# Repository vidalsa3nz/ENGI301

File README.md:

# ENGI301
<ENGI301>
Repository for ENGI301 course work

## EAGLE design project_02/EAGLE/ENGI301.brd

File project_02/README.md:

# ENGI 301: Etch A Sketch

This folder has files for the electronic components of the Etch A Sketch device including .sch, .brd, .lib, and other miscellaneous files.
For this project we were given components to go into the Etch A Sketch device and were tasked with creating the above files using symbols and footprints for each component.

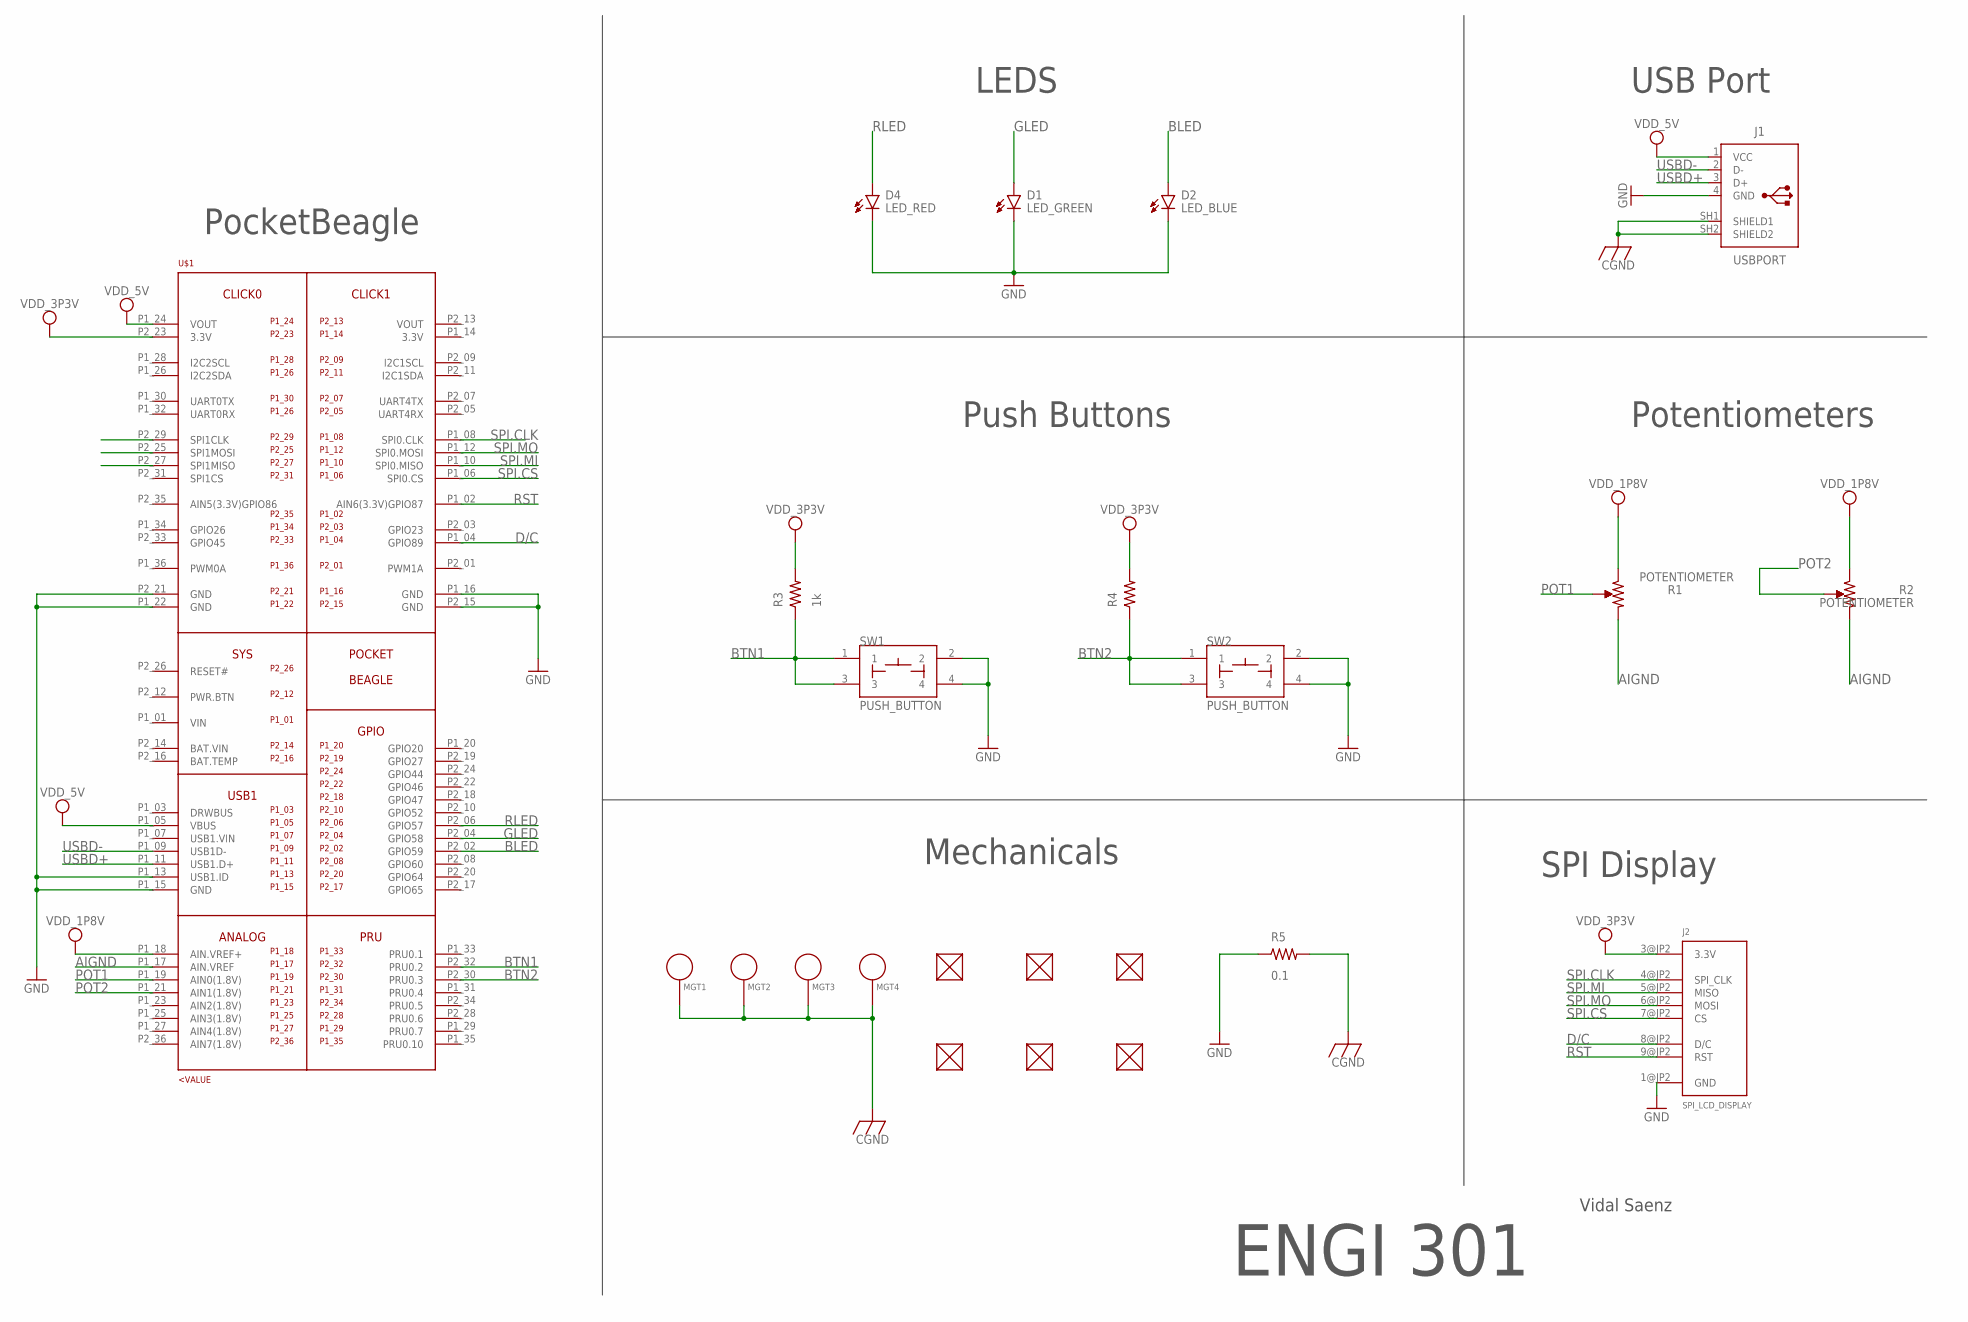
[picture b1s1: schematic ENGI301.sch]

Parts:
D1: LED_GREEN; LEDC3216X75N_FLAT-G
D2: LED_BLUE; LEDC3216X75N_FLAT-B
D4: LED_RED; LEDC3216X75N_FLAT-R
FUD1, FUD2, FUD3, FUD4, FUD5, FUD6: FIDUCIAL; FIDUCIAL_40MIL
J1: USBPORT; 1734366
J2: SPI_LCD_DISPLAY
MGT1, MGT2, MGT3, MGT4: MOUNTING_HOLE
R1, R2: POTENTIOMETER; POT-PO90S
R3: 1k; R1206
R4: R_R1206; R1206
R5: 0.1; R0603
SW1, SW2: PUSH_BUTTON; BUTTON_12.5MM
U$1: POCKETBEAGLE

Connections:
AIGND: R1.CW, R2.CW, U$1.P1_17 (AIN.VREF)
BLED: D2.A, U$1.P2_02 (GPIO59)
BTN1: R3.1, SW1.1, SW1.3, U$1.P2_32 (PRU0.2)
BTN2: R4.1, SW2.1, SW2.3, U$1.P2_30 (PRU0.3)
CGND: MGT1.P$1, MGT2.P$1, MGT3.P$1, MGT4.P$1, R5.2
D/C: J2.8@JP2 (D/C), U$1.P1_04 (GPIO89)
GLED: D1.A, U$1.P2_04 (GPIO58)
GND: J1.4 (GND), J2.1@JP2 (GND), R5.1, SW1.2, SW1.4, SW2.2, SW2.4, U$1.P1_13 (USB1.ID), U$1.P1_15 (GND), U$1.P1_16 (GND), U$1.P1_22 (GND), U$1.P2_15 (GND), U$1.P2_21 (GND)
unnamed: D1.C, D2.C, D4.C
POT1: R1.S, U$1.P1_19 (AIN0(1.8V))
POT2: R2.S, U$1.P1_21 (AIN1(1.8V))
RLED: D4.A, U$1.P2_06 (GPIO57)
RST: J2.9@JP2 (RST), U$1.P1_02 (AIN6(3.3V)GPIO87)
SHIELD2: J1.SH1 (SHIELD1), J1.SH2 (SHIELD2)
SPI.CLK: J2.4@JP2 (SPI_CLK), U$1.P1_08 (SPI0.CLK)
SPI.CS: J2.7@JP2 (CS), U$1.P1_06 (SPI0.CS)
SPI.MI: J2.5@JP2 (MISO), U$1.P1_10 (SPI0.MISO)
SPI.MO: J2.6@JP2 (MOSI), U$1.P1_12 (SPI0.MOSI)
USBD+: J1.3 (D+), U$1.P1_11 (USB1.D+)
USBD-: J1.2 (D-), U$1.P1_09 (USB1D-)
VDD_1P8V: R1.CCW, R2.CCW, U$1.P1_18 (AIN.VREF+)
VDD_3P3V: J2.3@JP2 (3.3V), R3.2, R4.2, U$1.P2_23 (3.3V)
VDD_5V: J1.1 (VCC), U$1.P1_05 (VBUS), U$1.P1_24 (VOUT)

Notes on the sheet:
PocketBeagle
SPI Display
USB Port
Push Buttons
Potentiometers
LEDS
Mechanicals
Vidal Saenz
ENGI 301

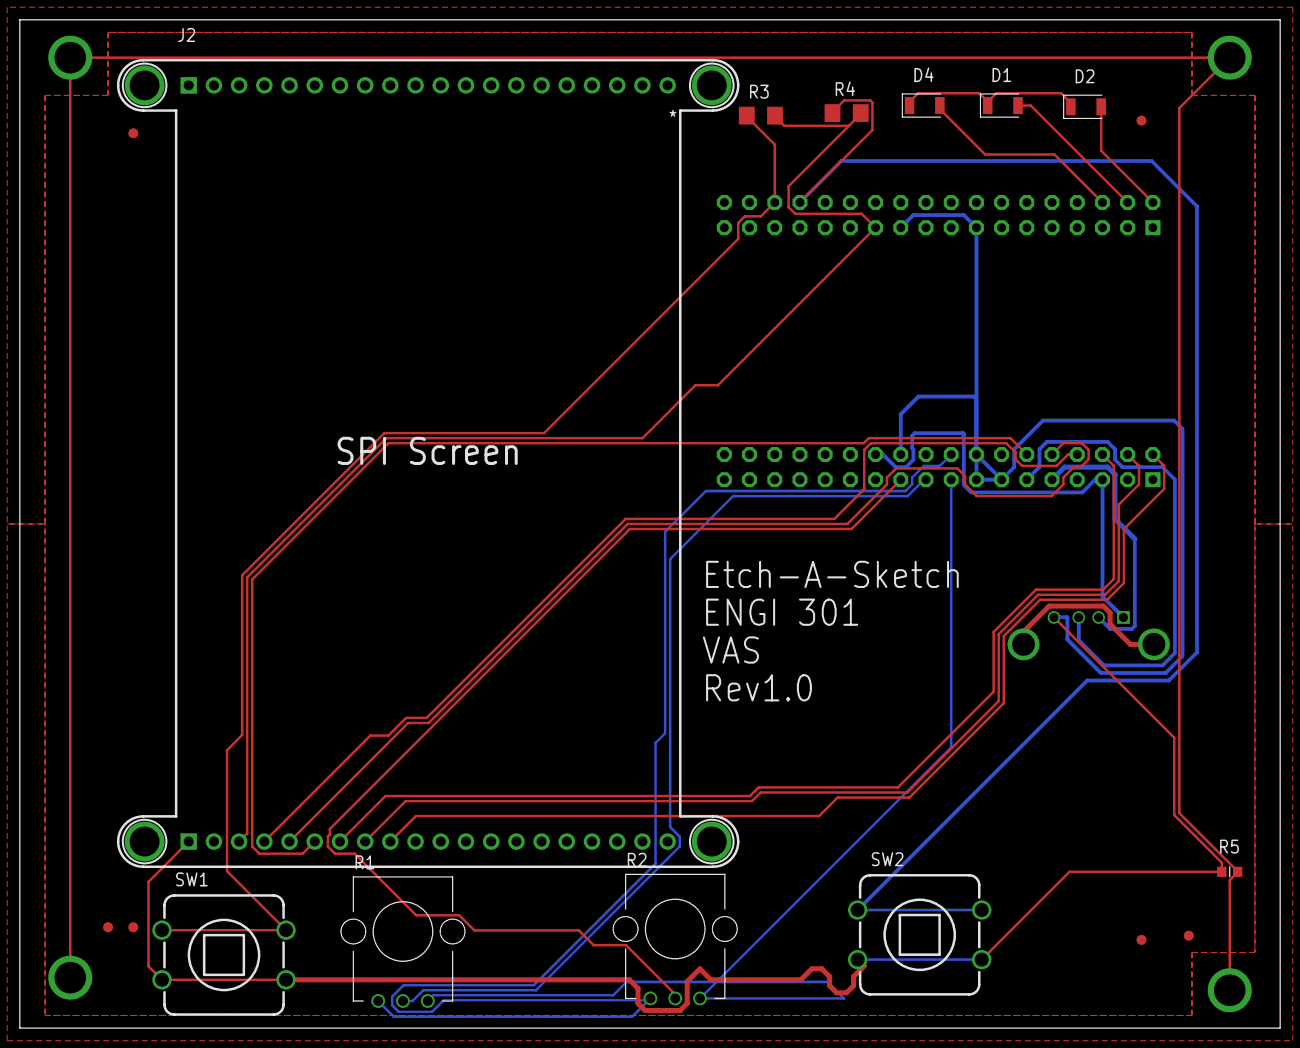
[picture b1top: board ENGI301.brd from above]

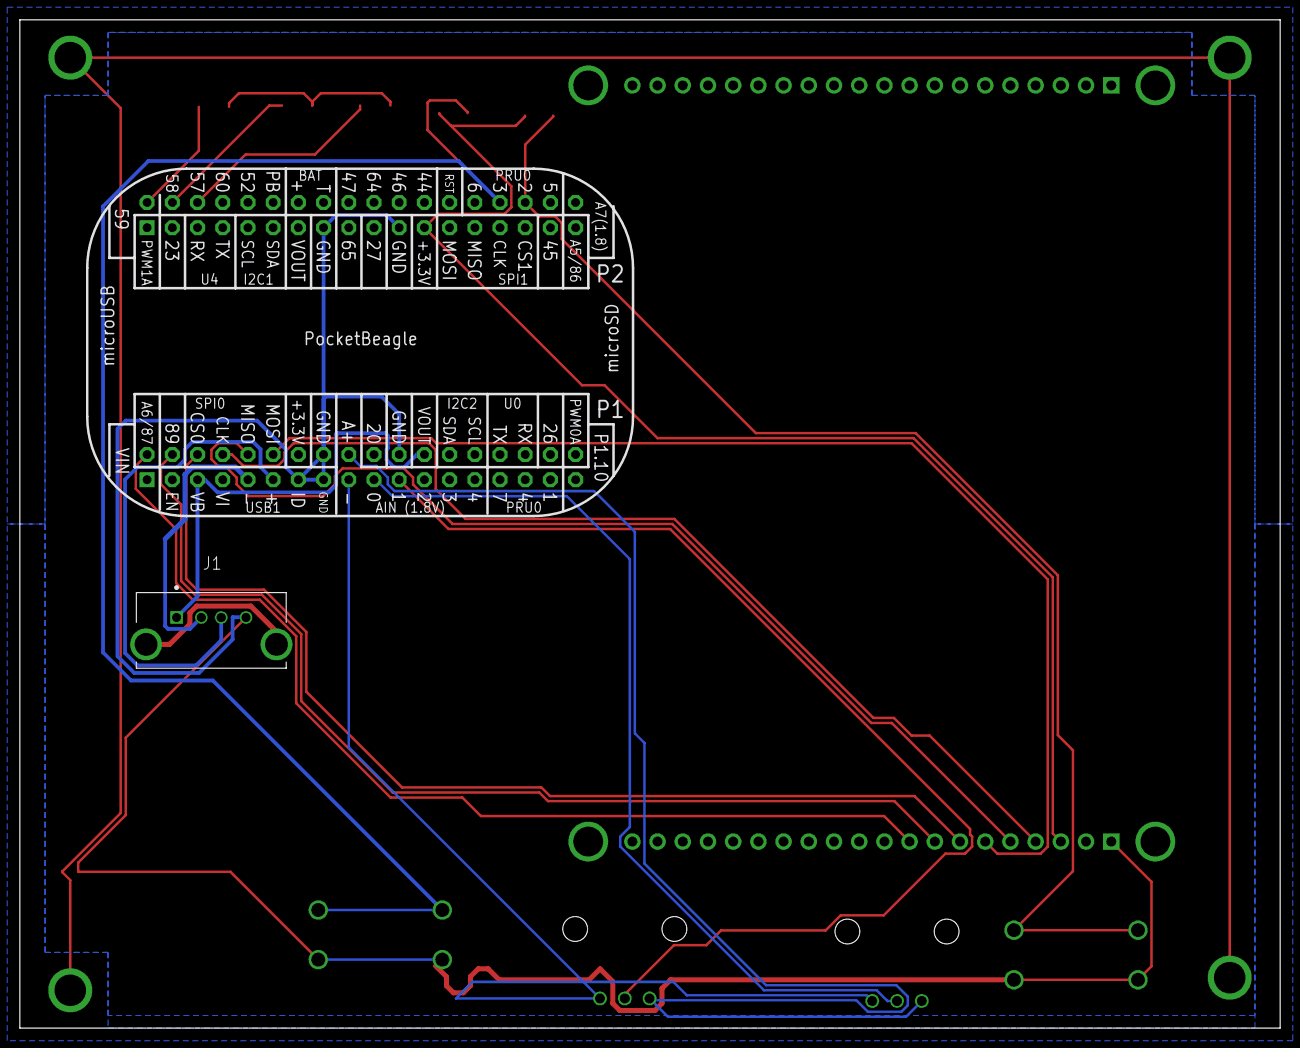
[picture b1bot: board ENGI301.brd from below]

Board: 4 copper layers, 127.0 x 101.6 mm, 23 parts (2 on the bottom side), 23 nets.

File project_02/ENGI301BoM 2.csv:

Part,Value,Device,Package,Description,CATEGORY,COLOR,CONTACTS,CURRENT_RATING,DESCRIPTION,GENDER,MANUFACTURER,MOUNT_TYPE,MPN,OPERATING_TEMP,PART_STATUS,ROHS_COMPLIANT,SERIES,SUB-CATEGORY,THERMALLOSS,TYPE,VALUE,VOLTAGE_RATING,
D1,LED_GREEN,LED_G_1206,LEDC3216X75N_FLAT-G,Green LED Light,LED,GREEN,,,CHIP LED FLAT,,,,,,,,,CHIP,,FLAT_TOP,LED_GREEN,,
D2,LED_BLUE,LED_B_1206,LEDC3216X75N_FLAT-B,Blue LED Light,LED,BLUE,,,CHIP LED FLAT,,,,,,,,,CHIP,,FLAT_TOP,LED_BLUE,,
D4,LED_RED,LED_R_1206,LEDC3216X75N_FLAT-R,Red LED Light,LED,RED,,,CHIP LED FLAT,,,,,,,,,CHIP,,FLAT_TOP,LED_RED,,
FUD1,FIDUCIAL,FIDUCIAL,FIDUCIAL_40MIL,40 MIL Fiducial,FUD,,,,,,,,,,,,,,,,,,
FUD2,FIDUCIAL,FIDUCIAL,FIDUCIAL_40MIL,40 MIL Fiducial,FUD,,,,,,,,,,,,,,,,,,
FUD3,FIDUCIAL,FIDUCIAL,FIDUCIAL_40MIL,40 MIL Fiducial,FUD,,,,,,,,,,,,,,,,,,
FUD4,FIDUCIAL,FIDUCIAL,FIDUCIAL_40MIL,40 MIL Fiducial,FUD,,,,,,,,,,,,,,,,,,
FUD5,FIDUCIAL,FIDUCIAL,FIDUCIAL_40MIL,40 MIL Fiducial,FUD,,,,,,,,,,,,,,,,,,
FUD6,FIDUCIAL,FIDUCIAL,FIDUCIAL_40MIL,40 MIL Fiducial,FUD,,,,,,,,,,,,,,,,,,
J1,USBPORT,USBPORT,1734366,"USB(2.0) Type-A, RCPT, 4POS, THT-VERT",Connector,,4,1A,CONN RCPT USB2.0 TYPEA 4POS VERT,Receptacle,TE Connectivity,Vertical,1734366-1,-40° to +80°C,Active,RoHS Compliant,-,USB,,USB-A,,30VAC(rms),
J2,SPI_LCD_DISPLAY,SPI_LCD_DISPLAY,SPI_LCD_DISPLAY,"2.8 Adafruit SPI Display""",SPI,,,,,,,,,,,,,,,,,,
MGT1,MOUNTING_HOLE,MOUNTING_HOLE,MOUNTING_HOLE,Chassis Mounting Hole w/GND connection ability,MH,,,,,,,,,,,,,,,,,,
MGT2,MOUNTING_HOLE,MOUNTING_HOLE,MOUNTING_HOLE,Chassis Mounting Hole w/GND connection ability,MH,,,,,,,,,,,,,,,,,,
MGT3,MOUNTING_HOLE,MOUNTING_HOLE,MOUNTING_HOLE,Chassis Mounting Hole w/GND connection ability,MH,,,,,,,,,,,,,,,,,,
MGT4,MOUNTING_HOLE,MOUNTING_HOLE,MOUNTING_HOLE,Chassis Mounting Hole w/GND connection ability,MH,,,,,,,,,,,,,,,,,,
R1,POTENTIOMETER,POTENTIOMETER,POT-PO90S,Potentiometer - Examples:,POT,,,,,,,,,,,,,,,,,,
R2,POTENTIOMETER,POTENTIOMETER,POT-PO90S,Potentiometer - Examples:,POT,,,,,,,,,,,,,,,,,,
R3,1k,R_R1206,R1206,"RESISTOR, American symbol",RES,,,,,,,,,,,,,,,,,,
R4,,R_R1206,R1206,"RESISTOR, American symbol",RES,,,,,,,,,,,,,,,,,,
R5,0.1,R_R0603,R0603,"RESISTOR, American symbol",RES,,,,,,,,,,,,,,,,,,
SW1,PUSH_BUTTON,PUSH_BUTTON,BUTTON_12.5MM,12.5 MM Push Button,BUT,,,,,,,,,,,,,,,,,,
SW2,PUSH_BUTTON,PUSH_BUTTON,BUTTON_12.5MM,12.5 MM Push Button,BUT,,,,,,,,,,,,,,,,,,
U$1,POCKETBEAGLE,POCKETBEAGLE,POCKETBEAGLE,Pocketbeagle microcontroller device,MC,,,,,,,,,,,,,,,,,,

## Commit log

2023-09-09 Updating README.md
2023-09-27 assignment 4 updates
2023-09-27 assignment 4 question 2
2023-09-28 Updated Assignment 4 Question 1 Code
2023-09-28 Assignment 4 Question 1 updates
2023-10-13 Create Project1
2023-10-13 new changes
2023-10-18 new python files including servo, potent., and led
2023-11-15 Commiting Project 1 Code
2023-11-15 adding README file
2023-12-14 Create Blank File
2023-12-14 ENGI301 Project2 Implementation Files
2023-12-14 Create blank
2023-12-14 MFG File upload
2023-12-14 Schematic PDF Upload
2023-12-14 Project 2 Bill of Materials
2023-12-14 Rename project_02/ENGI301.pdf to project_02/docs/ENGI301.pdf
2023-12-14 Mechanical block diagram ppt
2023-12-14 Top and Btm assembly print outs
